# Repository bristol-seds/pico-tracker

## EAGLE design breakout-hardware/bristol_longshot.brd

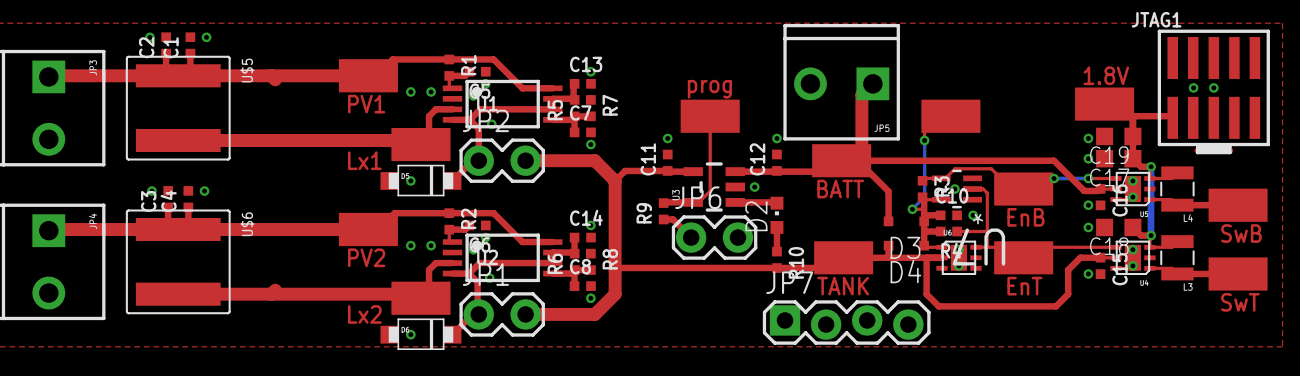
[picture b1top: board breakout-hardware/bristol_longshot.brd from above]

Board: 2 copper layers, 65 parts (0 on the bottom side), 23 nets.

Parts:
C1, C2, C3, C4, C11, C12, C13, C14, C15, C16: 4.7µF; _0402
C5, C6, C7, C8, C10: 1nF; _0402
C17, C18, C19: 10µF; C0603K
D2: GREEN; CHIPLED_0603
D3, D4: BAT760; SOD323
D5, D6: DIODE[TVS]; SOD123W
JP1, JP2: 1X02_LOCK
JP3: PV1; SCREWTERMINAL-3.5MM-2_LOCK
JP4: PV2; SCREWTERMINAL-3.5MM-2_LOCK
JP5: SCREWTERMINAL-3.5MM-2_LOCK
JP6: Shutdown; 1X02_LOCK
JP7: 1X04_LOCK
JTAG1: 2X05_1.27MM_SMT
L3, L4: 2.2µH; 1007
R1, R2: 1kΩ; _0402
R3, R4: 10kΩ; _0402
R5, R6: 220kΩ; _0402
R7, R8: 82kΩ; _0402
R9: 2.2kΩ; _0402
R10: 330Ω; _0402
U1, U2: SPV1040; TSSOP8
U3: LT4054ES5-4.2; SOT23-5
U4, U5: TPS62243; S-PWSON-N6
U6: TPS3808; S-PWSON-N6
U7: 74LVC1G04GW; SOT65P210X110-5N
U$5, U$6: XAL6060; XAL60
U$25, U$30, U$31, U$33, U$34, U$39, U$41, U$42, U$43, U$44, U$45, U$46, U$47: S1751-46R

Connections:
1.8V: C17.1, C18.1, C19.1, JTAG1.1, L3.2, L4.2, U4.3, U5.3, U$42.PAD
BATTERY: C12.1, C16.1, D3.A, JP5.1, U3.3, U5.5, U$39.PAD
BATTERY_BUCK_SW: L4.1, U5.1, U$46.PAD
BATTERY_EN: R3.1, U5.4, U7.4, U$44.PAD
CHG: D2.C, U3.1
CHG_LED: D2.A, R10.1
GND: C1.2, C2.2, C3.2, C4.2, C5.1, C6.1, C7.2, C8.2, C10.2, C11.2, C12.2, C13.2, C14.2, C15.2, C16.2, C17.2, C18.2, C19.2, D5.P$1, D6.P$1, JP3.2, JP4.2, JP5.2, JP6.2, JP7.1, JP7.2, JP7.3, JP7.4, JTAG1.3, JTAG1.5, R7.1, R8.1, U1.2, U2.2, U3.2, U4.2, U4.6, U4.PAD, U5.2, U5.6, U5.PAD, U6.5, U6.PAD, U7.3
LX1: U1.3, U$5.P$2, U$33.PAD
LX2: U2.3, U$6.P$2, U$34.PAD
MPP-SET2: C6.2, R2.2, U2.1
MPPT-VOUT-1: C13.1, D5.P$2, JP2.1, R5.2, U1.4, U1.6, U1.7
MPPT-VOUT-2: C14.1, D6.P$2, JP1.1, R6.2, U2.4, U2.6, U2.7
unnamed: C5.2, R1.2, U1.1
unnamed: JP6.1, R9.1
PROG: R9.2, U3.5, U$25.PAD
PV1: C1.1, C2.1, JP3.1, R1.1, U1.8, U$5.P$1, U$30.PAD
PV2: C3.1, C4.1, JP4.1, R2.1, U2.8, U$6.P$1, U$31.PAD
SPV_VCTRL1: C7.1, R5.1, R7.2, U1.5
SPV_VCTRL2: C8.1, R6.1, R8.2, U2.5
SUPERVISOR_VCC: C10.1, D3.C, D4.C, R3.2, R4.2, U6.1, U7.5, U$47.PAD
TANK: C11.1, C15.1, D4.A, JP1.2, JP2.2, R10.2, U3.4, U4.5, U6.2, U$41.PAD
TANK_BUCK_SW: L3.1, U4.1, U$45.PAD
TANK_EN: R4.1, U4.4, U6.6, U7.2, U$43.PAD

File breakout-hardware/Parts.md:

# Parts List

---

## Actives

| Part | Description | Supplier | Quantity Required | Notes
| ---  | ---         | ---       | ---               | ---
|SPV1040T|Voltage Regulators - Switching Regulators Hi efficiency solar battery charger|[511-SPV1040T](http://uk.mouser.com/Search/Refine.aspx?N=1323043&Keyword=51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|2|MPPT U1, U2
|LTC4054LES5-4.2#PBF|LINEAR TECHNOLOGY - CHARGER, BATTERY, LI-ION, 0.15A, 5SOT23|[2102610](http://uk.farnell.com/webapp/wcs/stores/servlet/Search?st=2102610)|1|Li-ion charge controller U3
|TPS62243DRVT|TEXAS INSTRUMENTS - DC-DC CONV, BUCK, 0.3A, 2.25MHZ, SON-6|[2400648](http://uk.farnell.com/webapp/wcs/stores/servlet/Search?st=2400648) [595-TPS62243DRVT](http://uk.mouser.com/Search/Refine.aspx?N=1323043&Keyword=59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|2|Buck Converter DRVT = SON-6 TPS62243 U4, U5
|TPS3808G25DRVR|Supervisory Circuits Lo Quies Current Pro Delay Sup Circuit|[595-TPS3808G25DRVR](http://uk.mouser.com/Search/Refine.aspx?N=1323043&Keyword=59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|1|Vth = 2.33, DRVR = SON-6 U6
|74LVC1G04GW,125|NXP - IC, LOGIC, INVERTER, SOT-353|[1631683](http://uk.farnell.com/webapp/wcs/stores/servlet/Search?st=1631683) [771-74LVC1G04GW-G](http://uk.mouser.com/Search/Refine.aspx?N=1323043&Keyword=77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|1|Inverter U7
|BAT760|NXP - DIODE, SCHOTTKY, SOD-323|[8734593](http://uk.farnell.com/webapp/wcs/stores/servlet/Search?st=8734593) [771-BAT760-T/R](http://uk.mouser.com/Search/Refine.aspx?N=1323043&Keyword=77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|2|D3, D4


## Passives

| Part | Description | Supplier | Quantity Required | Notes
| ---  | ---         | ---       | ---               | ---
|XAL6060-103MEC|COILCRAFT - INDUCTOR, PWR, 10UH, 7A,  20%, 14MHZ|[2289091](http://uk.farnell.com/webapp/wcs/stores/servlet/Search?st=2289091)|2|Recomended Lx for MPPT L1, L2
|SRN4026-100M|BOURNS - INDUCTOR, SEMI-SHLD, 10UH, 20%, 0.97A|[2428219](http://uk.farnell.com/webapp/wcs/stores/servlet/Search?st=2428219)|0|10µH Lx for MPPT 4x4mm 0.102Ω esr, try this L1, L2
|SRN2512-2R2M|BOURNS - INDUCTOR, SEMI-SHLD, 2.2UH, 20%, 2.3A|[2428203](http://uk.farnell.com/webapp/wcs/stores/servlet/Search?st=2428203)|0|2.2µH Lx for MPPT, try this L1, L2 <-- Doesn't work
|SRN2512-2R2M|BOURNS - INDUCTOR, SEMI-SHLD, 2.2UH, 20%, 2.3A|[2428203](http://uk.farnell.com/webapp/wcs/stores/servlet/Search?st=2428203)|2|Inductutor for Buck L3, L4
|C1005X5R0J475M050BC|TDK - CAP, MLCC, X5R, 4.7UF, 6.3V, 0402|[2309027](http://uk.farnell.com/webapp/wcs/stores/servlet/Search?st=2309027)|4|Solar input cap 4.7uF C1, C2, C3, C4
|C1005X5R0J475M050BC|TDK - CAP, MLCC, X5R, 4.7UF, 6.3V, 0402|[2309027](http://uk.farnell.com/webapp/wcs/stores/servlet/Search?st=2309027)|4|MPPT output cap 4.7µF C13, C14
|MC0402B102J500CT|MULTICOMP - CAP, MLCC, X7R, 1NF, 50V, 0402|[2320765](http://uk.farnell.com/webapp/wcs/stores/servlet/Search?st=2320765)|5|Mpp-set, vctrl, vcc-sup 1nF C5, C6, C7, C8, C10
|C1005X5R0J475M050BC|TDK - CAP, MLCC, X5R, 4.7UF, 6.3V, 0402|[2309027](http://uk.farnell.com/webapp/wcs/stores/servlet/Search?st=2309027)|2|Chg in / out 4.7µF C11, C12
|C1005X5R0J475M050BC|TDK - CAP, MLCC, X5R, 4.7UF, 6.3V, 0402|[2309027](http://uk.farnell.com/webapp/wcs/stores/servlet/Search?st=2309027)|2|Buck in 4.7µF C15, C16
|06036D106MAT2A|AVX - CAP, MLCC, X5R, 10UF, 6.3V, 0603|[1833804](http://uk.farnell.com/webapp/wcs/stores/servlet/Search?st=1833804)|3|Buck Out 10µF 0603 C17, C18, C19
|CRG0402F1K0|TE CONNECTIVITY - RESISTOR, FIXED, 1K0, 1%, 0402|[2331474](http://uk.farnell.com/webapp/wcs/stores/servlet/Search?st=2331474)|2|Mpp-set R1, R2
|CRG0402F10K|TE CONNECTIVITY - RESISTOR, PRECISION, 10K, 1%, 0402|[2331444](http://uk.farnell.com/webapp/wcs/stores/servlet/Search?st=2331444)|2|en-pull-up R3, R4
|CRG0402F220K|TE CONNECTIVITY - RESISTOR, FIXED, 220K, 1%, 0402|[2331487](http://uk.farnell.com/webapp/wcs/stores/servlet/Search?st=2331487)|2|Vctrl-up R5, R6
|CRG0402F82K|TE CONNECTIVITY - RESISTOR, FIXED, 82K, 1%, 0402|[2331569](http://uk.farnell.com/webapp/wcs/stores/servlet/Search?st=2331569)|2|Vctrl-down R7, R8
|CRG0402F2K2|TE CONNECTIVITY - RESISTOR, FIXED, 2K2, 1%, 0402|[2331502](http://uk.farnell.com/webapp/wcs/stores/servlet/Search?st=2331502)|1|Rprog R9
|CRG0402F330R|TE CONNECTIVITY - RESISTOR, FIXED, 330R, 1%, 0402|[2331511](http://uk.farnell.com/webapp/wcs/stores/servlet/Search?st=2331511)|1|led R10
|PTVS5V0S1UR|NXP - DIODE, TVS, UNI, 5V, 400W, SOD123W|[1829262](http://uk.farnell.com/webapp/wcs/stores/servlet/Search?st=1829262)|2|TVS diodes D5, D6

## Items used in breakout verision ONLY

| Part | Description | Supplier | Quantity Required | Notes
| ---  | ---         | ---       | ---               | ---
|S1751-46R|HARWIN - TEST POINT, PCB, SMT|[2293786](http://uk.farnell.com/webapp/wcs/stores/servlet/Search?st=2293786)|12|Test Point
|CTB3051/2BK|CAMDENBOSS - TERMINAL BLOCK, WIRE TO BRD, 2POS|[3882615](http://uk.farnell.com/webapp/wcs/stores/servlet/Search?st=3882615)|3|Terminal Block 2 Wire
|CTB3051/3BK|CAMDENBOSS - TERMINAL BLOCK, WIRE TO BRD, 3POS|[3882627](http://uk.farnell.com/webapp/wcs/stores/servlet/Search?st=3882627)|0|Terminal Block 3 Wire
| D1, D2 | LED | | 2 | Misc

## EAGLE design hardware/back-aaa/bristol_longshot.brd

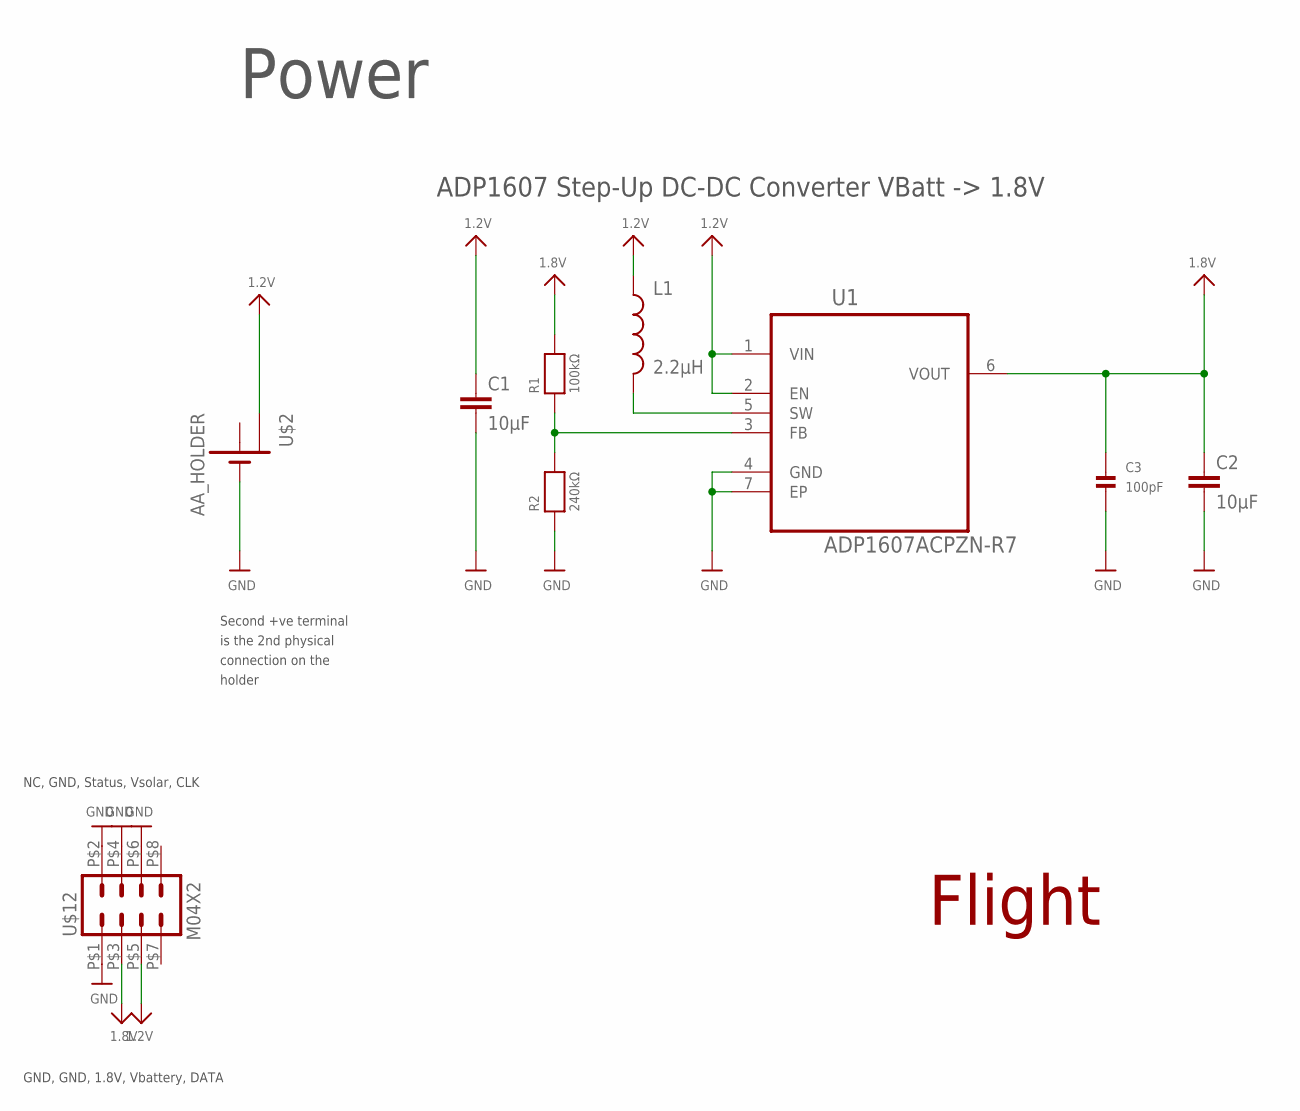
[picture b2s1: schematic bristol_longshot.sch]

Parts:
C1, C2: 10µF; C0603K
C3: 100pF; _0402
L1: 2.2µH; 1007
R1: 100kΩ; _0402
R2: 240kΩ; _0402
U1: ADP1607ACPZN-R7; DFN200X200X60-7N
U$2: AA_HOLDER; AA
U$12: M04X2

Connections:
1.2V: C1.1, L1.1, U1.1 (VIN), U1.2 (EN), U$2.+1 (+2), U$12.P$5 (5)
1.8V: C2.1, C3.1, R1.2, U1.6 (VOUT), U$12.P$3 (3)
+: U$2.+2 (+)
FB: R1.1, R2.2, U1.3 (FB)
GND: C1.2, C2.2, C3.2, R2.1, U1.4 (GND), U1.7 (EP), U$2.-1 (-), U$2.-2 (-), U$12.P$1 (1), U$12.P$2 (2), U$12.P$4 (4), U$12.P$6 (6)
SW: L1.2, U1.5 (SW)

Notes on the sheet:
ADP1607 Step-Up DC-DC Converter VBatt -> 1.8V
Power
Flight
Second +ve terminal is the 2nd physical connection on the holder
NC, GND, Status, Vsolar, CLK
GND, GND, 1.8V, Vbattery, DATA

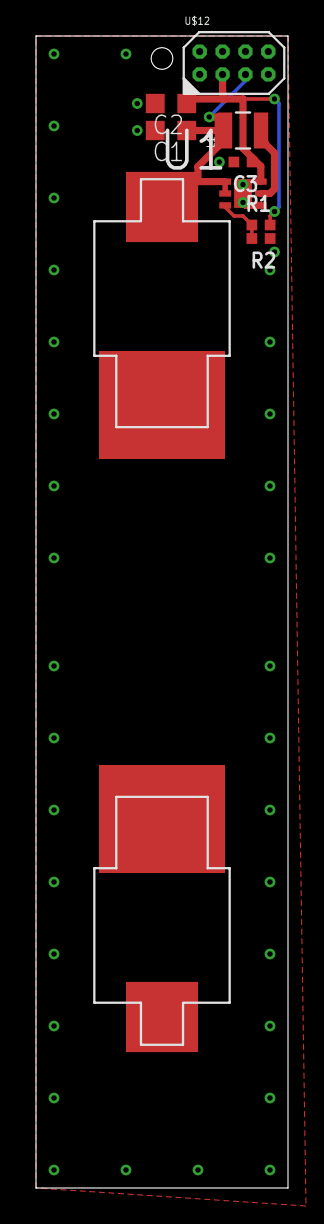
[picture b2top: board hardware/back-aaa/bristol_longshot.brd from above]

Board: 2 copper layers, 14.0 x 64.0 mm, 9 parts (0 on the bottom side), 5 nets.

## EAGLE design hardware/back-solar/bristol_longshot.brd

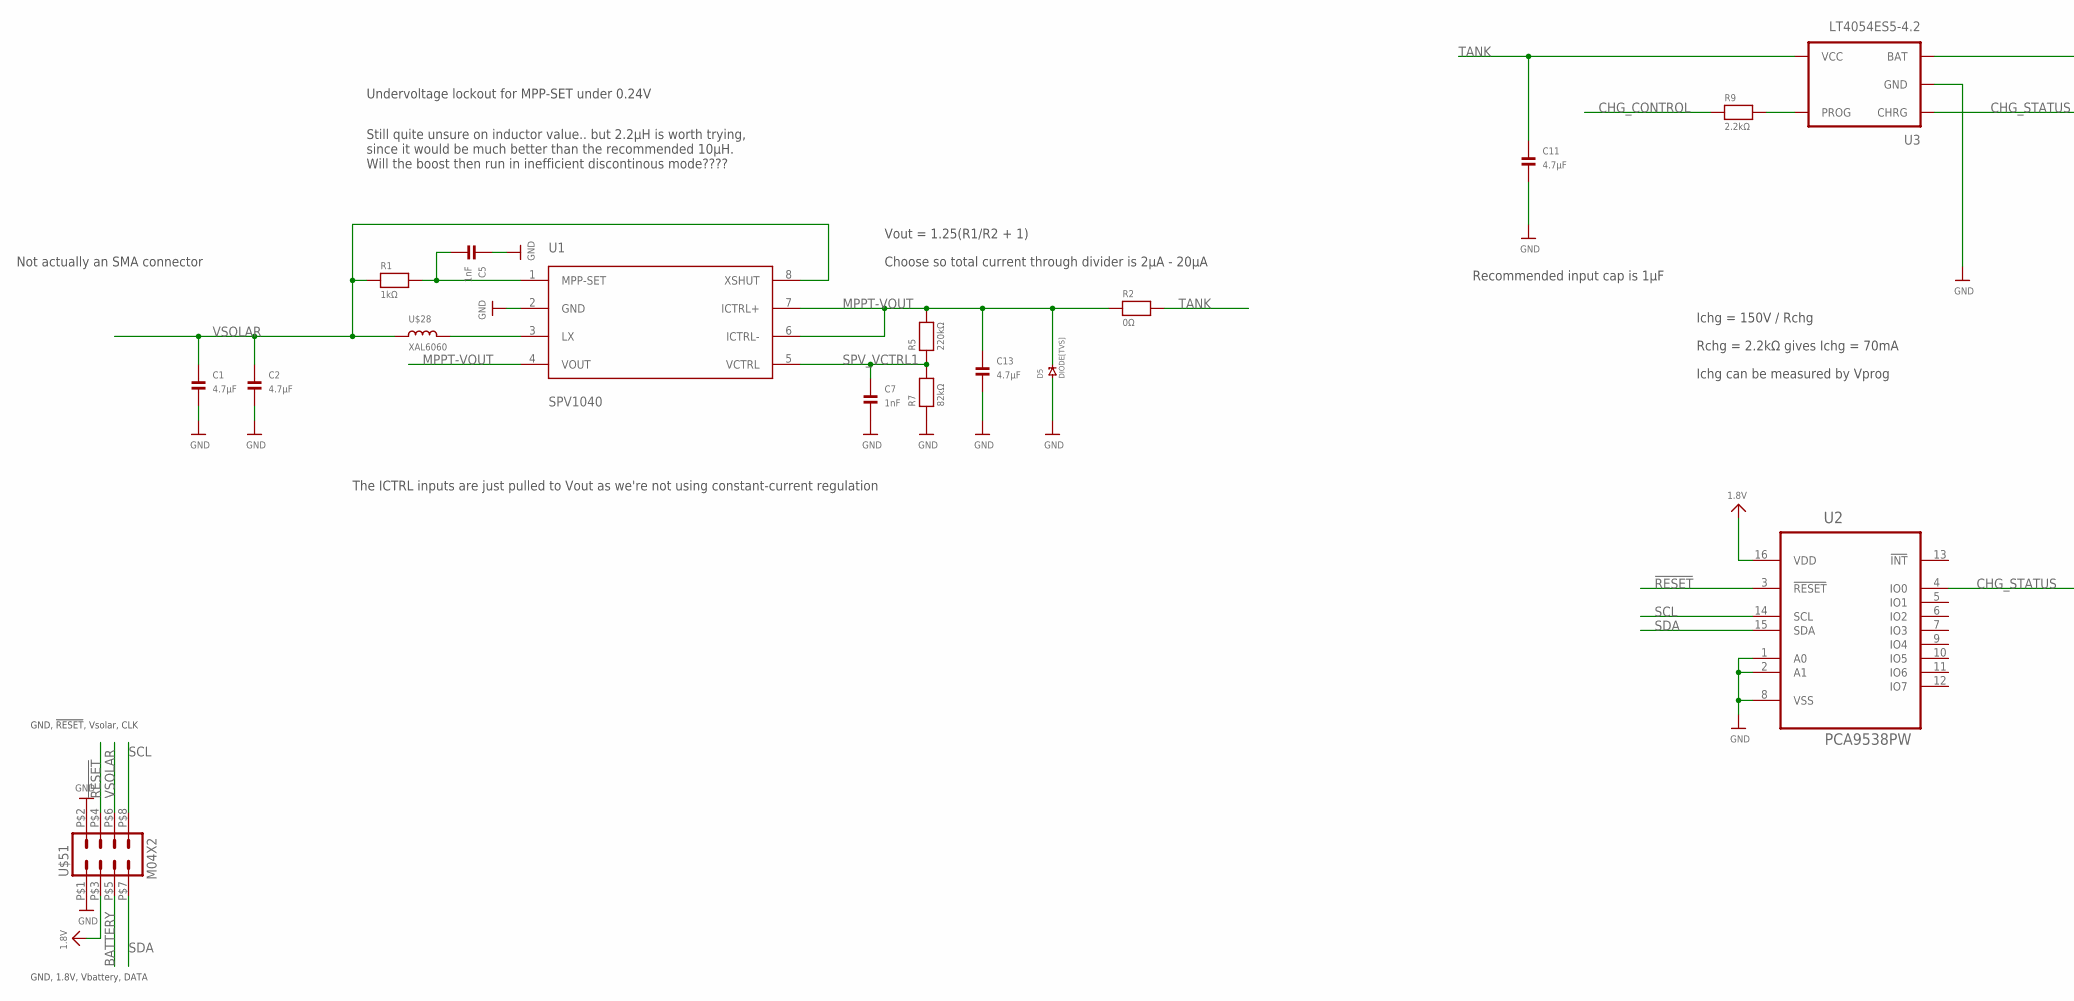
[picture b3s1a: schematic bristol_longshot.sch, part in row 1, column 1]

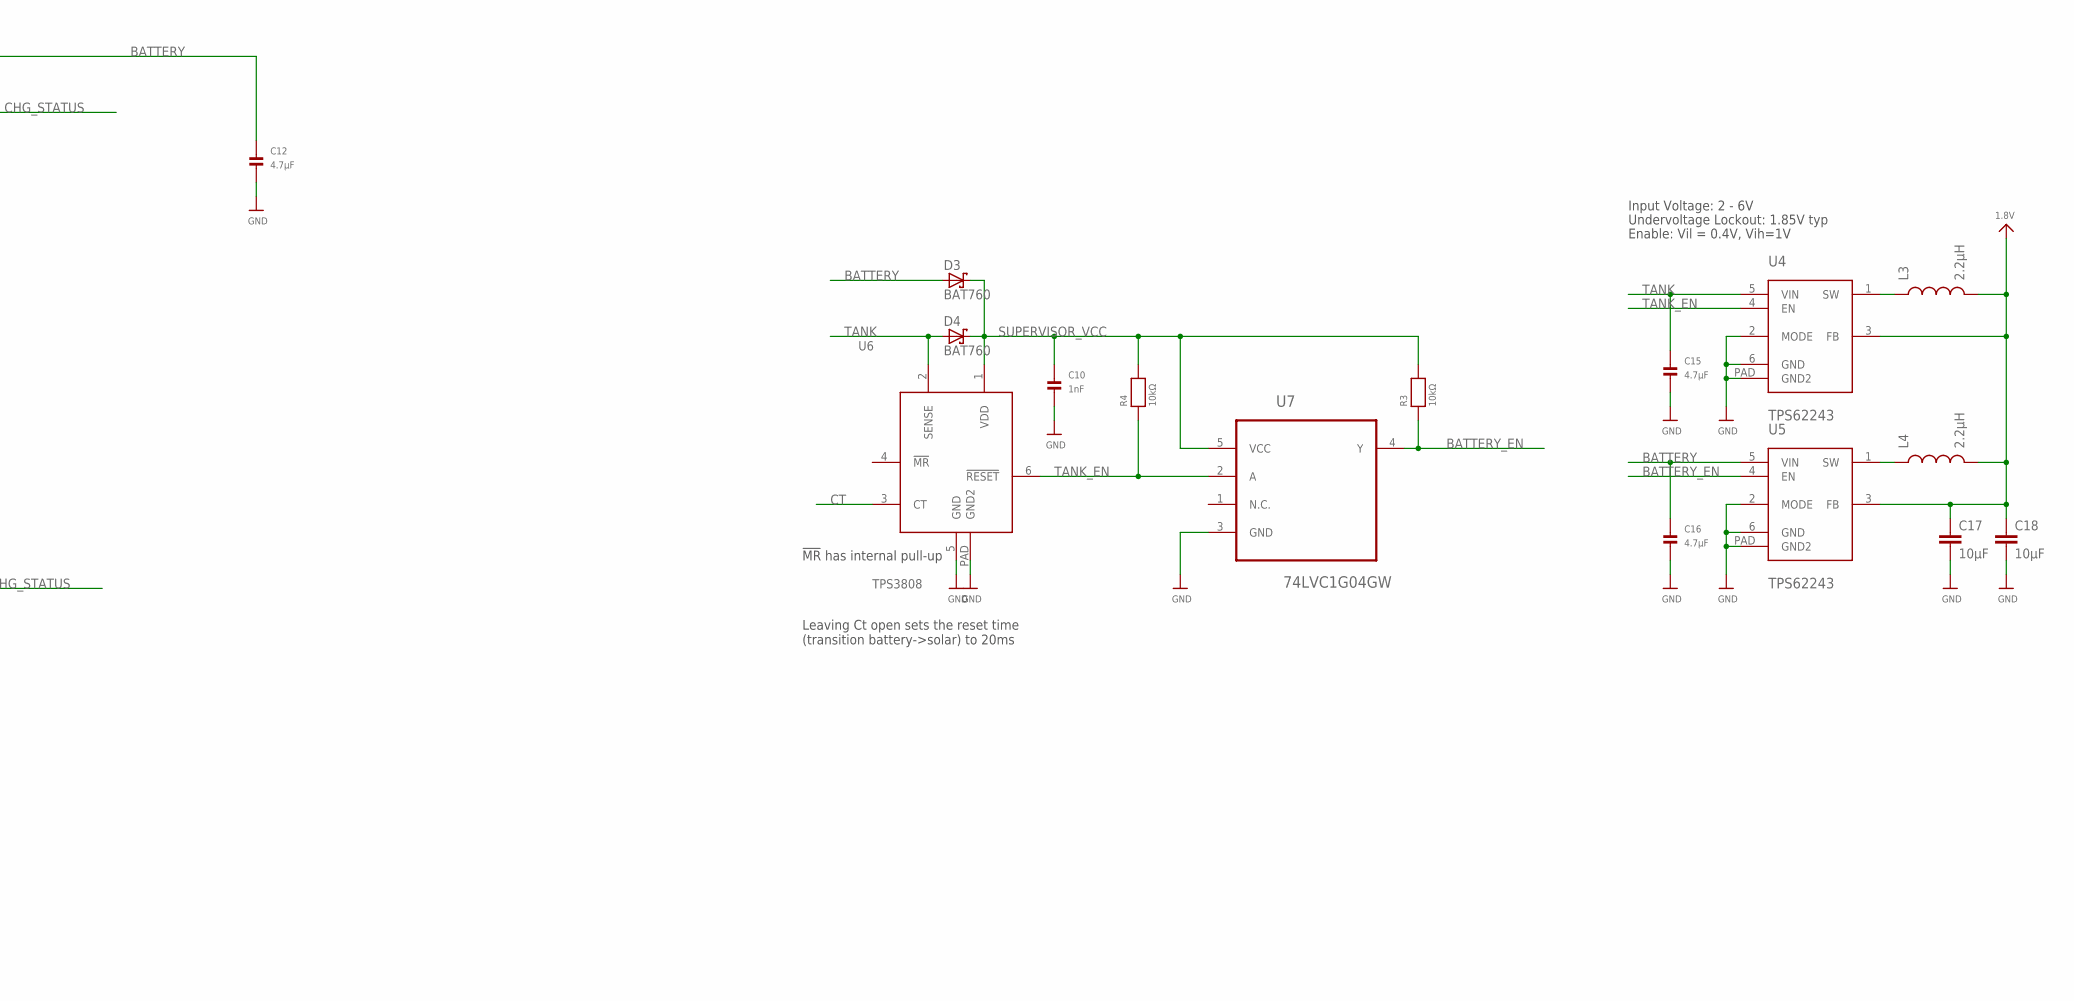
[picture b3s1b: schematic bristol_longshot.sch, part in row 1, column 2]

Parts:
C1, C2, C11, C12, C13, C15, C16: 4.7µF; _0402
C5, C7, C10: 1nF; _0402
C17, C18: 10µF; C0603K
D3, D4: BAT760; SOD323
D5: DIODE[TVS]; SOD123W
L3, L4: 2.2µH; 1007
R1: 1kΩ; _0402
R2: 0Ω; _0402
R3, R4: 10kΩ; _0402
R5: 220kΩ; _0402
R7: 82kΩ; _0402
R9: 2.2kΩ; _0402
U1: SPV1040; TSSOP8
U2: PCA9538PW; SOP65P640X110-16N
U3: LT4054ES5-4.2; SOT23-5
U4, U5: TPS62243; S-PWSON-N6
U6: TPS3808; S-PWSON-N6
U7: 74LVC1G04GW; SOT65P210X110-5N
U$28: XAL6060; XAL60
U$51: M04X2

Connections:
1.8V: C17.1, C18.1, L3.2, L4.2, U2.16 (VDD), U4.3 (FB), U5.3 (FB), U$51.P$3 (3)
!RESET: U2.3 (!RESET), U$51.P$4 (4)
BATTERY: C12.1, C16.1, D3.A, U3.3 (BAT), U5.5 (VIN), U$51.P$5 (5)
BATTERY_BUCK_SW: L4.1, U5.1 (SW)
BATTERY_EN: R3.1, U5.4 (EN), U7.4 (Y)
CHG_CONTROL: R9.1
CHG_STATUS: U2.4 (IO0), U3.1 (CHRG)
CT: U6.3 (CT)
GND: C1.2, C2.2, C5.1, C7.2, C10.2, C11.2, C12.2, C13.2, C15.2, C16.2, C17.2, C18.2, D5.P$1 (1), R7.1, U1.2 (GND), U2.1 (A0), U2.2 (A1), U2.8 (VSS), U3.2 (GND), U4.2 (MODE), U4.6 (GND), U4.PAD (GND2), U5.2 (MODE), U5.6 (GND), U5.PAD (GND2), U6.5 (GND), U6.PAD (GND2), U7.3 (GND), U$51.P$1 (1), U$51.P$2 (2)
LX1: U1.3 (LX), U$28.P$2 (2)
MPP-SET: C5.2, R1.2, U1.1 (MPP-SET)
MPPT-VOUT: C13.1, D5.P$2 (2), R2.1, R5.2, U1.4 (VOUT), U1.6 (ICTRL-), U1.7 (ICTRL+)
PROG: R9.2, U3.5 (PROG)
SCL: U2.14 (SCL), U$51.P$8 (8)
SDA: U2.15 (SDA), U$51.P$7 (7)
SPV_VCTRL1: C7.1, R5.1, R7.2, U1.5 (VCTRL)
SUPERVISOR_VCC: C10.1, D3.C, D4.C, R3.2, R4.2, U6.1 (VDD), U7.5 (VCC)
TANK: C11.1, C15.1, D4.A, R2.2, U3.4 (VCC), U4.5 (VIN), U6.2 (SENSE)
TANK_BUCK_SW: L3.1, U4.1 (SW)
TANK_EN: R4.1, U4.4 (EN), U6.6 (!RESET), U7.2 (A)
VSOLAR: C1.1, C2.1, R1.1, U1.8 (XSHUT), U$28.P$1 (1), U$51.P$6 (6)

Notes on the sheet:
Input Voltage: 2 - 6V
Enable: Vil = 0.4V, Vih=1V
Undervoltage Lockout: 1.85V typ
Undervoltage lockout for MPP-SET under 0.24V
Still quite unsure on inductor value.. but 2.2µH is worth trying, since it would be much better than the recommended 10µH. Will the boost then run in inefficient discontinous mode????
The ICTRL inputs are just pulled to Vout as we're not using constant-current regulation
Leaving Ct open sets the reset time (transition battery->solar) to 20ms
Recommended input cap is 1µF
Ichg = 150V / Rchg
!MR! has internal pull-up
Rchg = 2.2kΩ gives Ichg = 70mA
Ichg can be measured by Vprog
Vout = 1.25(R1/R2 + 1)
Choose so total current through divider is 2µA - 20µA
GND, !RESET!, Vsolar, CLK
GND, 1.8V, Vbattery, DATA
Not actually an SMA connector

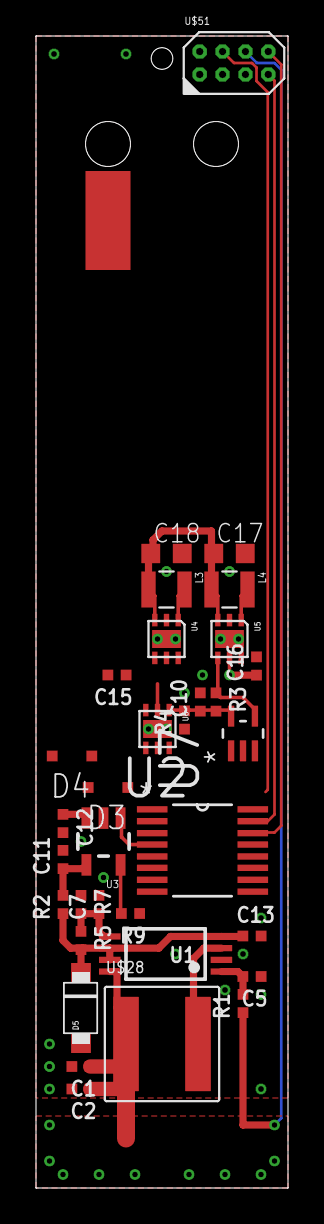
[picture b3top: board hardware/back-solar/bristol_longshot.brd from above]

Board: 2 copper layers, 14.0 x 64.0 mm, 33 parts (0 on the bottom side), 19 nets.

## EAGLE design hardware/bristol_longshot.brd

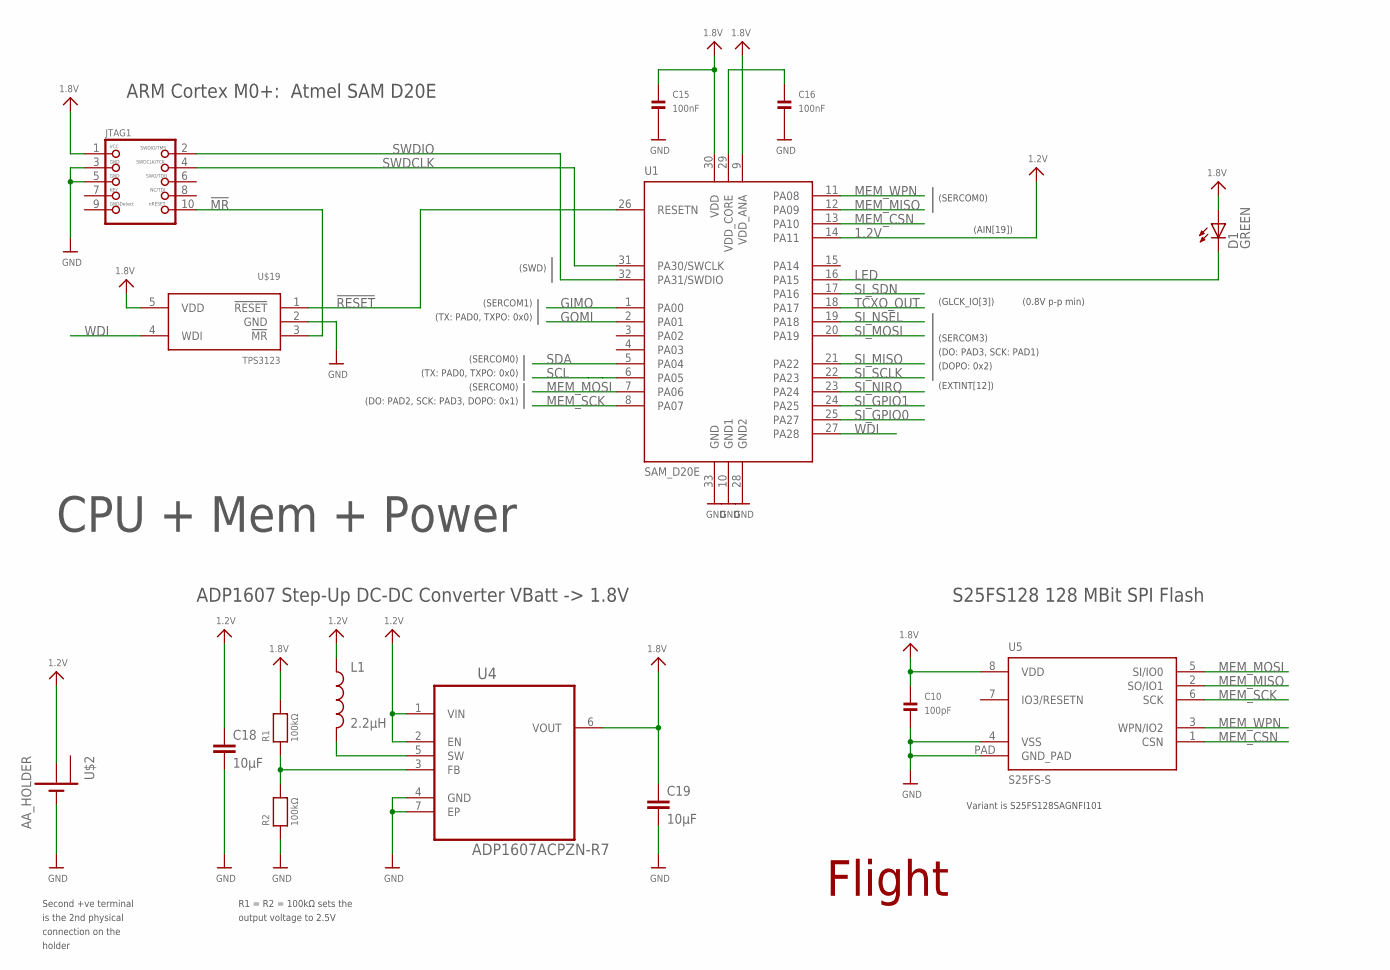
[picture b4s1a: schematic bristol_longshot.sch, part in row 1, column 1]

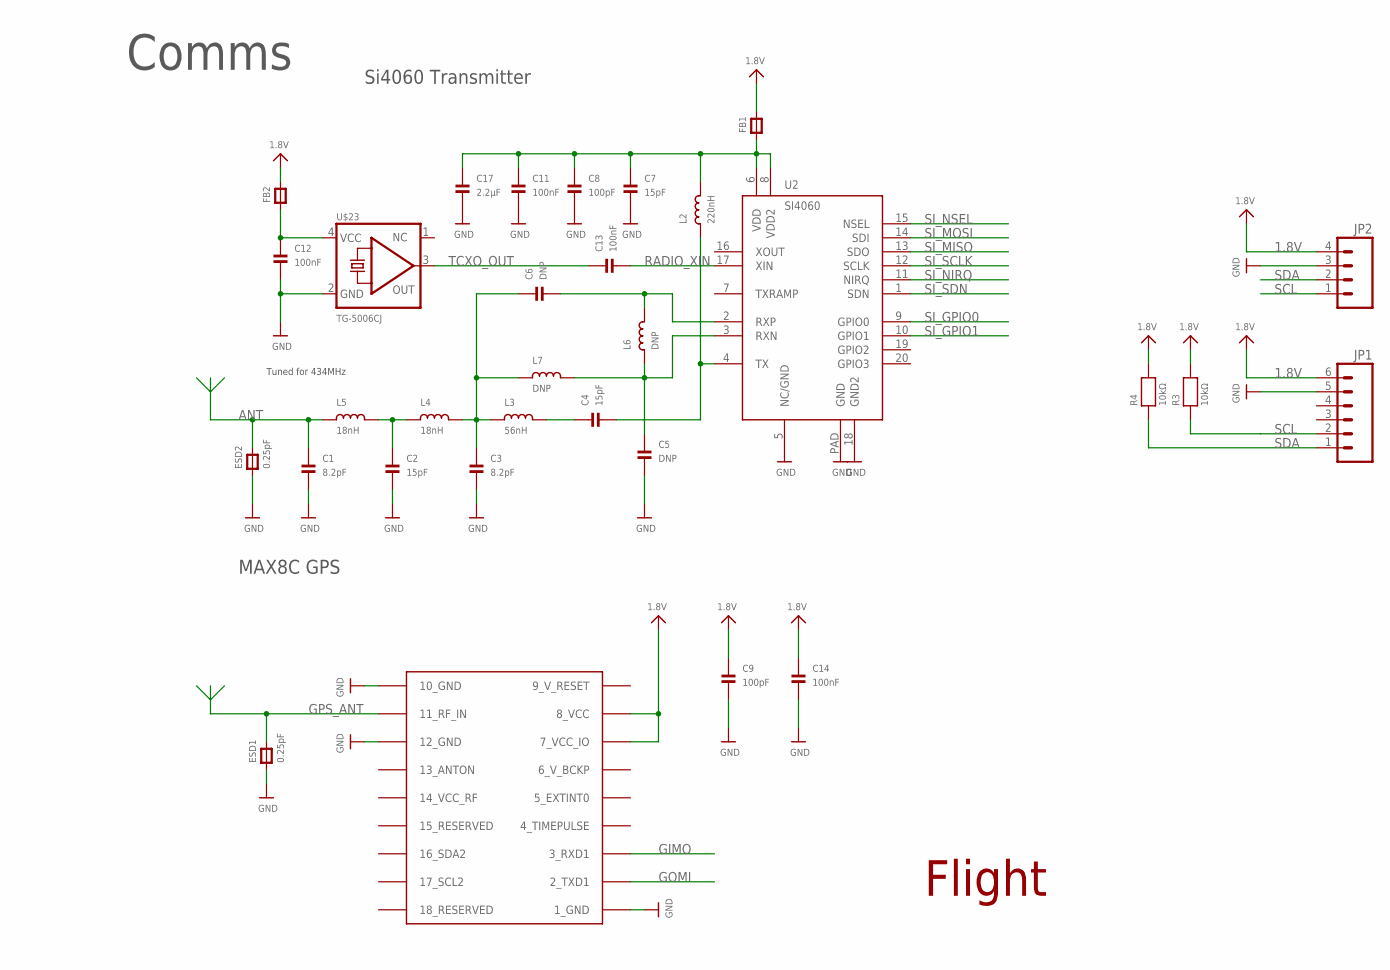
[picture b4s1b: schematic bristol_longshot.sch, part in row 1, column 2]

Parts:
C1, C3: 8.2pF; _0402
C2, C4, C7: 15pF; _0402
C5, C6: DNP; _0402
C8, C9, C10: 100pF; _0402
C11, C12, C13, C14, C15, C16: 100nF; _0402
C17: 2.2µF; _0402
C18, C19: 10µF; C0603K
D1: GREEN; CHIPLED_0603
ESD1, ESD2: 0.25pF; _0603MP
FB1, FB2: FERRITE_0402; _0402
JP1: M06LOCK; 1X06_LOCK
JP2: M04LOCK; 1X04_LOCK
JTAG1: JTAG-CORTEXM3SMT; 2X05_1.27MM_SMT
L1: 2.2µH; 1007
L2: 220nH; _0402
L3: 56nH; _0402
L4, L5: 18nH; _0402
L6, L7: DNP; _0402
R1, R2: 100kΩ; _0402
R3, R4: 10kΩ; _0402
U1: SAM_D20E; QFN32_5MM
U2: SI4060; QFN20
U4: ADP1607ACPZN-R7; DFN200X200X60-7N
U5: S25FS-S; WSON8
U$2: AA_HOLDER; AA
U$19: TPS3123; SOT23-5
U$23: TG-5006CJ; TC-5006CJ
U$48: UBLOX_MAX

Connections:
1.2V: C18.1, L1.1, U1.14 (PA11), U4.1 (VIN), U4.2 (EN), U$2.+2 (+)
1.8V: C9.1, C10.1, C14.1, C15.1, C19.1, D1.A, FB1.2, FB2.2, JP1.6, JP2.4, JTAG1.1, R1.2, R3.2, R4.2, U1.9 (VDD_ANA), U1.30 (VDD), U4.6 (VOUT), U5.8 (VDD), U$19.5 (VDD), U$48.7_VCC_IO, U$48.8_VCC
9_V_RESET: U$48.9_V_RESET
!MR: JTAG1.10, U$19.3 (!MR)
!RESET: U1.26 (RESETN), U$19.1 (!RESET)
+2: U$2.+1 (+2)
ANT: C1.1, ESD2.2, L5.1
FB: R1.1, R2.2, U4.3 (FB)
FILTER1: C3.1, C6.1, L3.1, L4.2, L7.1
FILTER2: C2.1, L4.1, L5.2
GIMO: U1.1 (PA00), U$48.3_RXD1
GND: C1.2, C2.2, C3.2, C5.2, C7.2, C8.2, C9.2, C10.2, C11.2, C12.2, C14.2, C15.2, C16.2, C17.2, C18.2, C19.2, ESD1.1, ESD2.1, JP1.5, JP2.3, JTAG1.3, JTAG1.5, R2.1, U1.10 (GND1), U1.28 (GND2), U1.33 (GND), U2.5 (NC/GND), U2.18 (GND2), U2.PAD (GND), U4.4 (GND), U4.7 (EP), U5.4 (VSS), U5.PAD (GND_PAD), U$2.-1 (-), U$2.-2 (-), U$19.2 (GND), U$23.2 (GND), U$48.1_GND, U$48.10_GND, U$48.12_GND
GOMI: U1.2 (PA01), U$48.2_TXD1
GPS_ANT: ESD1.2, U$48.11_RF_IN
LED: D1.C, U1.16 (PA15)
MEM_CSN: U1.13 (PA10), U5.1 (CSN)
MEM_MISO: U1.12 (PA09), U5.2 (SO/IO1)
MEM_MOSI: U1.7 (PA06), U5.5 (SI/IO0)
MEM_SCK: U1.8 (PA07), U5.6 (SCK)
MEM_WPN: U1.11 (PA08), U5.3 (WPN/IO2)
unnamed: JP1.1, JP2.2, R4.1, U1.5 (PA04)
RADIO_VDD: C7.1, C8.1, C11.1, C17.1, FB1.1, L2.2, U2.6 (VDD), U2.8 (VDD2)
RADIO_XIN: C13.2, U2.17 (XIN)
RF_OUT: C4.2, L2.1, U2.4 (TX)
RXN: C5.1, L6.1, L7.2, U2.3 (RXN)
RXP: C6.2, L6.2, U2.2 (RXP)
SI_GPIO0: U1.25 (PA27), U2.9 (GPIO0)
SI_GPIO1: U1.24 (PA25), U2.10 (GPIO1)
SI_MISO: U1.21 (PA22), U2.13 (SDO)
SI_MOSI: U1.20 (PA19), U2.14 (SDI)
SI_NIRQ: U1.23 (PA24), U2.11 (NIRQ)
SI_NSEL: U1.19 (PA18), U2.15 (NSEL)
SI_SCLK: U1.22 (PA23), U2.12 (SCLK)
SI_SDN: U1.17 (PA16), U2.1 (SDN)
SW: L1.2, U4.5 (SW)
SWDCLK: JTAG1.4, U1.31 (PA30/SWCLK)
SWDIO: JTAG1.2, U1.32 (PA31/SWDIO)
TANK: C4.1, L3.2
TCXO_OUT: C13.1, U1.18 (PA17), U$23.3 (OUT)
TCXO_VDD: C12.1, FB2.1, U$23.4 (VCC)
TIMEPULSE: JP1.2, JP2.1, R3.1, U1.6 (PA05), U$48.4_TIMEPULSE
VDD_CORE: C16.1, U1.29 (VDD_CORE)
WDI: U1.27 (PA28), U$19.4 (WDI)

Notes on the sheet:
ARM Cortex M0+: Atmel SAM D20E
(SERCOM3)
(SWD)
(SERCOM0)
(EXTINT[12])
(DO: PAD3, SCK: PAD1)
(DOPO: 0x2)
(DO: PAD2, SCK: PAD3, DOPO: 0x1)
(SERCOM1)
(TX: PAD0, TXPO: 0x0)
ADP1607 Step-Up DC-DC Converter VBatt -> 1.8V
(AIN[19])
S25FS128 128 MBit SPI Flash
Variant is S25FS128SAGNFI101
MAX8C GPS
Si4060 Transmitter
Tuned for 434MHz
CPU + Mem + Power
Comms
Flight
Second +ve terminal is the 2nd physical connection on the holder
(GLCK_IO[3])
(0.8V p-p min)
R1 = R2 = 100kΩ sets the output voltage to 2.5V

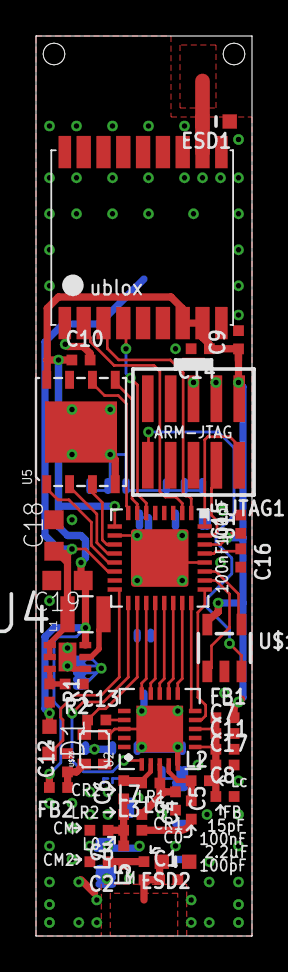
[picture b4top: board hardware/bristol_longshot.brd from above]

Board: 2 copper layers, 12.0 x 50.0 mm, 42 parts (1 on the bottom side), 40 nets.

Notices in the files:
parts and their libraries:
microbuilder_v3: This work is placed in the public domain, and may be freely used for commercial and non-commercial work with the following conditions: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
SparkFun: Licensing: CC v3.0 Share-Alike You are welcome to use this library for commercial purposes.
